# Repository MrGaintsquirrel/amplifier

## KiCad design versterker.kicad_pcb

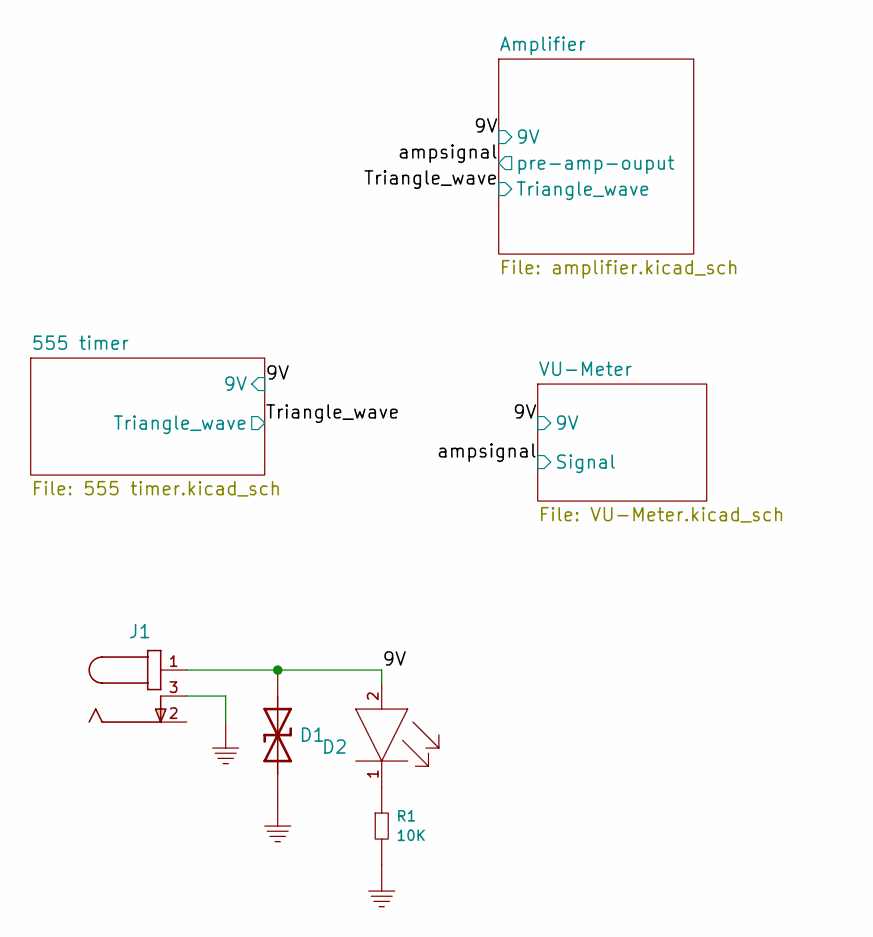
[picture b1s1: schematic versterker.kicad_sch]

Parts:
D1: D_SMCJ9.0CA_TVS; D_9V_TVS_SMCJ-Q; PARTREV 11/20/15; Mouser 576-SMCJ9.0CA
D2: D_RED_0603_Wurth_150060RS75000; D_RED_0603_Wurth; Mouser 710-150060RS75000
J1: J_Barreljack_3.5mm_Wurth_TH; J_Barreljack_3.5mm_Wurth; Mouser 710-694102303002
R1: R_10K_0603; R_0603; Mouser 667-ERJ-UP3F1002V

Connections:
/9V: D1.1, D2.2 (ANODE), J1.1; also elsewhere on the board
GND: D1.2, J1.3, R1.2; also elsewhere on the board
unnamed: D2.1 (CATHODE), R1.1

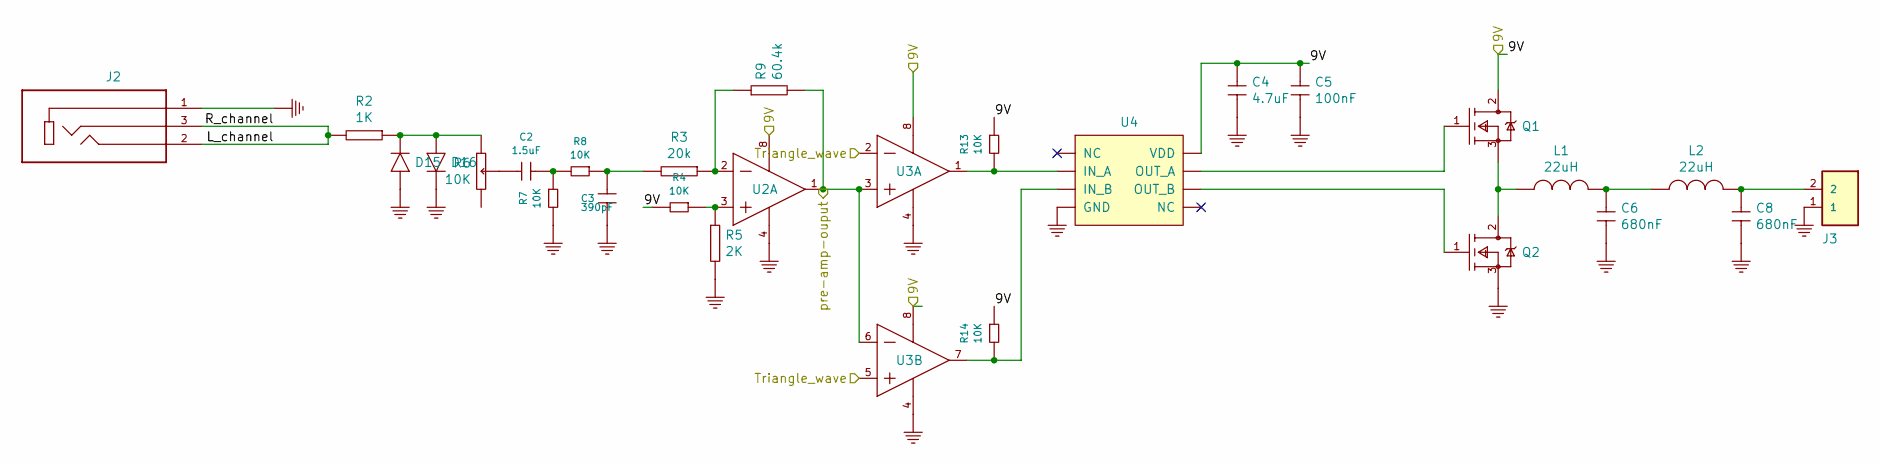
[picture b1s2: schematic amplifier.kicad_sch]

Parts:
C2: C_1.5uF_0603_25V; C_0603; Mouser 810-C1608X5R1E155K
C3: C_390pF_0603_50V; C_0603; Mouser 80-C0603C391K5R
C4: C_4.7uF_0603_25V; C_0603; Mouser 963-TMK107BBJ475KA-T
C5: C_100nF_0603_25V; C_0603; Mouser 810-C0603X5R1E104KBB
C6, C8: C_680nF_TH_450V; C_ECWFD_Panasonic; Mouser 667-ECW-FD2W684J
D15, D16: D_1N4148WS_SOD323F_ONSEMI; D_1N4148_SOD-323F_ONSEMI; Mouser 512-1N4148WS
J2: J_3.5mm_jack_SJ1-3523N; CUI_SJ1-3523N; Mouser 490-SJ1-3523N
J3: J_2_screwterminal_2.54_282834-2; J_2_screwterminal_2.54; Mouser 571-282834-2
L1, L2: L_22uH_RFS1113_coilcraft_TH; L_RFS1113_coilcraft; Mouser 994-RFS1113-223ME
Q1, Q2: Q_IRFZ44NPBF_N-Channel_Infineon; Q_IRFZ44NPBF_Infineon; Mouser 942-IRFZ44NPBF
R2: R_1K_0603; R_0603; Mouser 667-ERJ-PB3D1001V
R3: R_20K_0603; R_0603; Mouser 603-RT0603FRE0720KL
R4, R7, R8, R13, R14: R_10K_0603; R_0603; Mouser 667-ERJ-UP3F1002V
R5: R_2K_0603; R_0603; Mouser 603-RT0603BRD072KL
R6: R_10K_Potmeter; R_TH_POT_P160series
R9: R_60.4K_0603; R_0603; Mouser 603-RT0603DRE0760K4L
U2: U_LM358AP_TI_DIP; Mouser 926-LM358N/NOPB
U3: U_LM393N_NOPB; U_TI_LM393N_NOPB; Mouser 926-LM393N/NOPB
U4: U_TC4427M_Microchip; U_8_DIP_TC4427CPA_Microchip; Mouser 579-TC4427ACPA

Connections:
/9V: C4.1, C5.1, Q1.2 (DRAIN), R4.2, R13.1, R14.1, U2.8 (VCC), U3.8 (V+), U4.6 (VDD); also elsewhere on the board
/Amplifier/L_channel: J2.2, J2.3, R2.2
/Triangle_wave: U3.2 (INA-), U3.5 (INB+); also elsewhere on the board
/ampsignal: R9.2, U2.1 (1OUT), U3.3 (INA+), U3.6 (INB-); also elsewhere on the board
GND: C3.2, C4.2, C5.2, C6.2, C8.2, D15.A, D16.C, J2.1, J3.1, Q2.3 (SOURCE), R5.2, R7.2, U2.4 (GND), U3.4 (GND), U4.3 (GND); also elsewhere on the board
unnamed: C2.1, R7.1, R8.2
unnamed: C2.2, R6.2 (S)
unnamed: C3.1, R3.2, R8.1
unnamed: C6.1, L1.2, L2.1
unnamed: C8.1, J3.2, L2.2
unnamed: D15.C, D16.A, R2.1, R6.1
unnamed: L1.1, Q1.3 (SOURCE), Q2.2 (DRAIN)
unnamed: Q1.1 (GATE), U4.7 (OUT_A)
unnamed: Q2.1 (GATE), U4.5 (OUT_B)
unnamed: R3.1, R9.1, U2.2 (1IN-)
unnamed: R4.1, R5.1, U2.3 (1IN+)
unnamed: R13.2, U3.1 (OUTA), U4.2 (IN_A)
unnamed: R14.2, U3.7 (OUTB), U4.4 (IN_B)

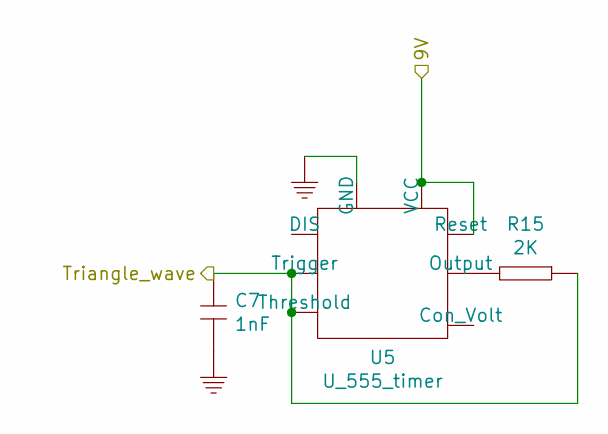
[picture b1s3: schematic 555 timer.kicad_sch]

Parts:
C7: C_1nF_0603_50V; C_0603; Mouser 603-CC603MRX7R9BB102
R15: R_2K_0603; R_0603; Mouser 603-RT0603BRD072KL
U5: U_555_timer; U_LM555CN

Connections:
/9V: U5.4 (Reset), U5.8 (VCC); also elsewhere on the board
/Triangle_wave: C7.1, R15.1, U5.2 (Trigger), U5.6 (Threshold); also elsewhere on the board
GND: C7.2, U5.1 (GND); also elsewhere on the board
unnamed: R15.2, U5.3 (Output)

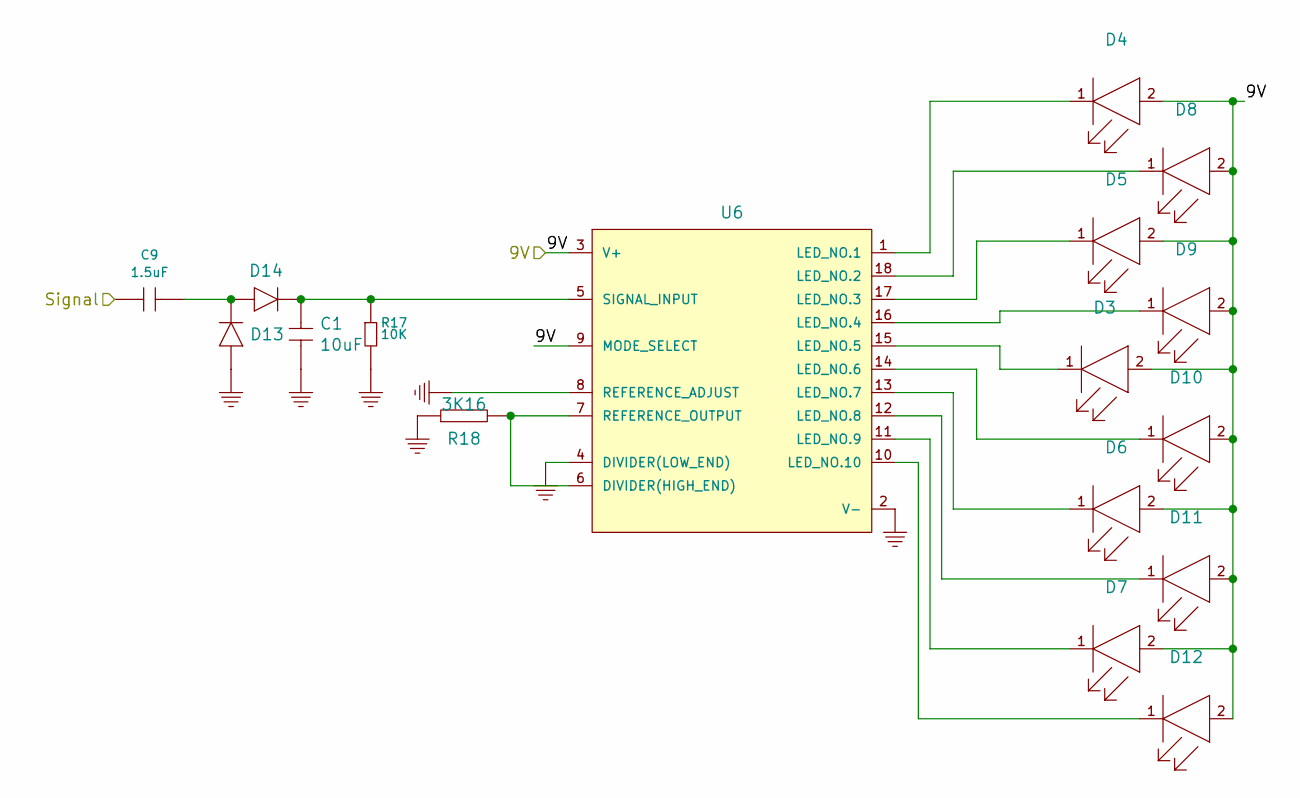
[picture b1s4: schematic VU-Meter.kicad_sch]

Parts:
C1: C_10uF_0603_16V; C_0603; Mouser 187-CL10A106KO8NQNC
C9: C_1.5uF_0603_25V; C_0603; Mouser 810-C1608X5R1E155K
D3, D4, D5, D6, D7, D8, D9, D10, D11, D12: D_RED_0603_Wurth_150060RS75000; D_RED_0603_Wurth; Mouser 710-150060RS75000
D13, D14: D_1N4148WS_SOD323F_ONSEMI; D_1N4148_SOD-323F_ONSEMI; Mouser 512-1N4148WS
R17: R_10K_0603; R_0603; Digi-key YAG1236CT-ND
R18: R_3K16_0603; R_0603; Mouser 603-RT0603BRD073K16L
U6: U_LM3914N-1_NOPB; U_LM3914_TI_DIP; Mouser 926-LM3914N-1/NOPB

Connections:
/9V: D3.2 (ANODE), D4.2 (ANODE), D5.2 (ANODE), D6.2 (ANODE), D7.2 (ANODE), D8.2 (ANODE), D9.2 (ANODE), D10.2 (ANODE), D11.2 (ANODE), D12.2 (ANODE), U6.3 (V+), U6.9 (MODE_SELECT); also elsewhere on the board
/ampsignal: C9.2; also elsewhere on the board
GND: C1.2, D13.A, R17.2, R18.1, U6.2 (V-), U6.4 (DIVIDER(LOW_END)), U6.8 (REFERENCE_ADJUST); also elsewhere on the board
unnamed: C1.1, D14.C, R17.1, U6.5 (SIGNAL_INPUT)
unnamed: C9.1, D13.C, D14.A
unnamed: D3.1 (CATHODE), U6.15 (LED_NO.5)
unnamed: D4.1 (CATHODE), U6.1 (LED_NO.1)
unnamed: D5.1 (CATHODE), U6.17 (LED_NO.3)
unnamed: D6.1 (CATHODE), U6.13 (LED_NO.7)
unnamed: D7.1 (CATHODE), U6.11 (LED_NO.9)
unnamed: D8.1 (CATHODE), U6.18 (LED_NO.2)
unnamed: D9.1 (CATHODE), U6.16 (LED_NO.4)
unnamed: D10.1 (CATHODE), U6.14 (LED_NO.6)
unnamed: D11.1 (CATHODE), U6.12 (LED_NO.8)
unnamed: D12.1 (CATHODE), U6.10 (LED_NO.10)
unnamed: R18.2, U6.6 (DIVIDER(HIGH_END)), U6.7 (REFERENCE_OUTPUT)

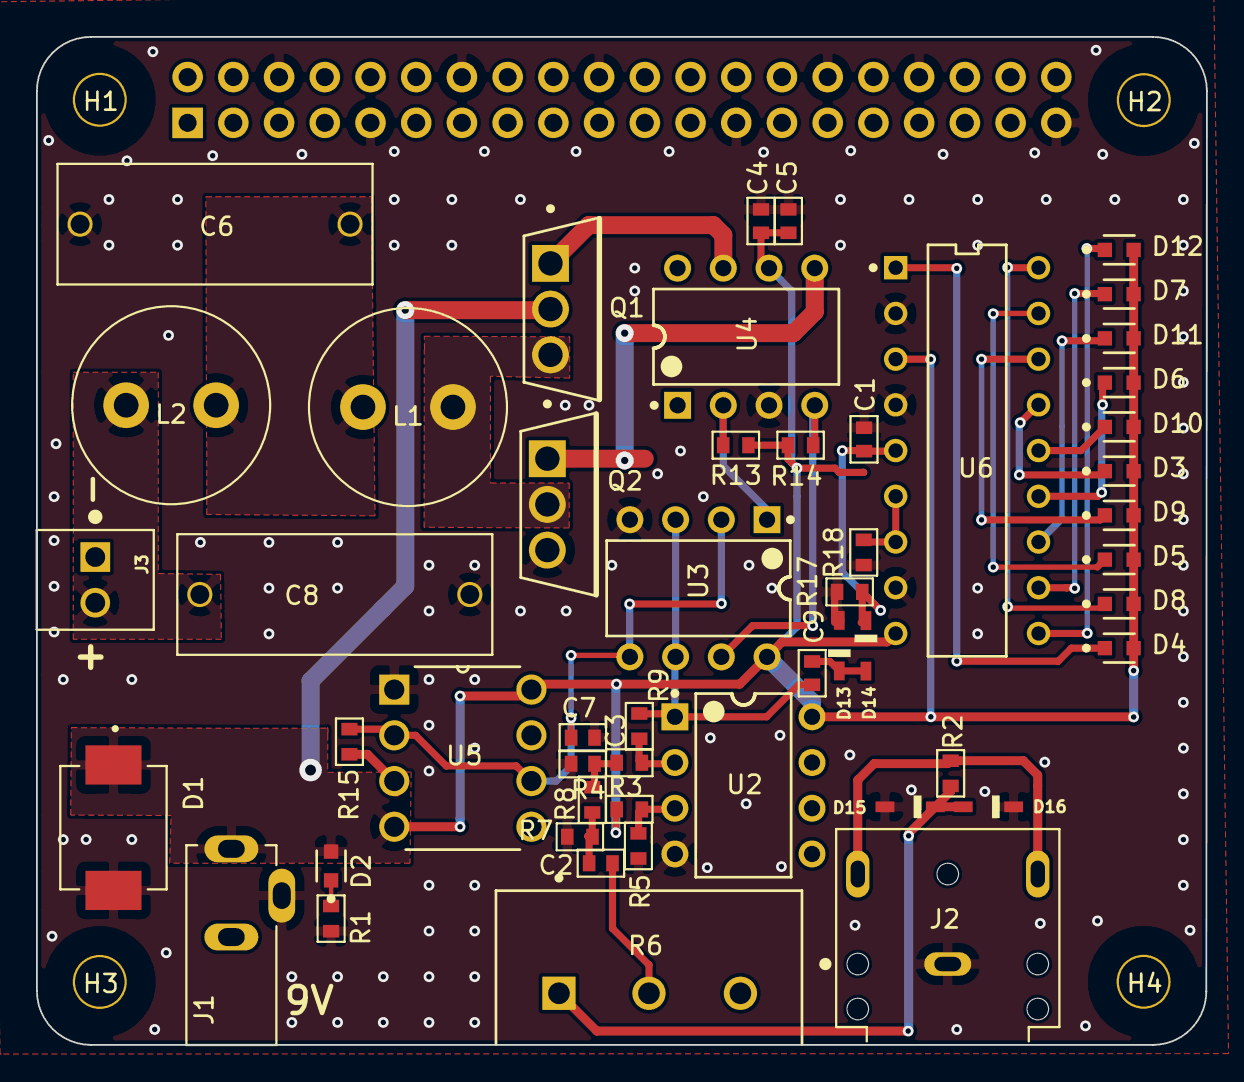
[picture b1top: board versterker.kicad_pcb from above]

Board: 2 copper layers, 65.0 x 56.0 mm, 56 parts (1 on the bottom side), 34 nets.

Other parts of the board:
H1, H2, H3, H4: 3mm_Mounting_Hole; NPTH_3mm_ID
J3#2: 40HAT; PinSocket_2x20_P2.54mm_Vertical

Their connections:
/P5V_HAT: J3#2.2, J3#2.4
GND: J3#2.6, J3#2.9, J3#2.14, J3#2.20, J3#2.25, J3#2.30, J3#2.34, J3#2.39; also elsewhere on the board

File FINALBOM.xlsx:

Ref | Qnty | Waarde | Cmp name | Footprint | Description | Mouser
C1, | 1 | C_10uF_0603_16V | C_10uF_0603_16V | MAIN_PCB_LIB:C_0603 |  | 187-CL10A106KO8NQNC
C2,C9, | 2 | C_1.5uF_0603_25V | C_1.5uF_0603_25V | MAIN_PCB_LIB:C_0603 |  | 810-C1608X5R1E155K
C3, | 1 | C_390pF_0603_50V | C_390pF_0603_50V | MAIN_PCB_LIB:C_0603 |  | 80-C0603C391K5R
C4, | 1 | C_4.7uF_0603_25V | C_4.7uF_0603_25V | Main_LIB:C_0603 |  | 963-TMK107BBJ475KA-T
C5, | 1 | C_100nF_0603_25V | C_100nF_0603_25V | MAIN_PCB_LIB:C_0603 |  | 810-C0603X5R1E104KBB
C6,C8, | 2 | C_680nF_TH_450V | C_680nF_TH_450V | MAIN_PCB_LIB:C_ECWFD_Panasonic |  | 667-ECW-FD2W684J
C7, | 1 | C_1nF_0603_50V | C_1nF_0603_50V | MAIN_PCB_LIB:C_0603 |  | 581-06035A102J
D1, | 1 | D_SMCJ9.0CA_TVS | D_SMCJ9.0CA_TVS | MAIN_PCB_LIB:D_9V_TVS_SMCJ-Q |  | 576-SMCJ9.0CA
D2,D3,D4,D5,D6,D7,D8,D9,D10,D11,D12, | 11 | D_RED_0603_Wurth_150060RS75000 | D_RED_0603_Wurth_150060RS75000 | MAIN_PCB_LIB:D_RED_0603_Wurth |  | 710-150060RS75000
D13,D14,D15,D16, | 4 | D_1N4148WS_SOD323F_ONSEMI | D_1N4148WS_SOD323F_ONSEMI | MAIN_PCB_LIB:D_1N4148_SOD-323F_ONSEMI |  | 512-1N4148WS
J1, | 1 | J_Barreljack_3.5mm_Wurth_TH | J_Barreljack_3.5mm_Wurth_TH | MAIN_PCB_LIB:J_Barreljack_3.5mm_Wurth |  | 710-694102303002
J2, | 1 | J_3.5mm_jack_SJ1-3523N | J_3.5mm_jack_SJ1-3523N | CUI_SJ1-3523N |  | 490-SJ1-3523N
J3, | 1 | J_2_screwterminal_2.54_282834-2 | J_2_screwterminal_2.54_282834-2 | MAIN_PCB_LIB:J_2_screwterminal_2.54 |  | 571-282834-2
L1,L2, | 2 | L_22uH_RFS1113_coilcraft_TH | L_22uH_RFS1113_coilcraft_TH | MAIN_PCB_LIB:L_RFS1113_coilcraft |  | 994-RFS1113-223ME
Q1,Q2, | 2 | Q_IRFZ44NPBF_N-Channel_Infineon | Q_IRFZ44NPBF_N-Channel_Infineon | MAIN_PCB_LIB:Q_IRFZ44NPBF_Infineon |  | 942-IRFZ44NPBF
R1,R4,R7,R8,R13,R14,R17, | 7 | R_10K_0603 | R_10K_0603 | MAIN_PCB_LIB:R_0603 |  | 603-AC0603FR-1010KL
R2, | 1 | R_1K_0603 | R_1K_0603 | MAIN_PCB_LIB:R_0603 |  | 603-AC0603FR-071KL
R3, | 1 | R_20K_0603 | R_20K_0603 | MAIN_PCB_LIB:R_0603 |  | 603-RT0603FRE0720KL
R5,R15, | 2 | R_2K_0603 | R_2K_0603 | MAIN_PCB_LIB:R_0603 |  | 603-RT0603FRE072KL
R6, | 1 | R_10K_Potmeter | R_10K_Potmeter | MAIN_PCB_LIB:R_TH_POT_P160series
R9, | 1 | R_60.4K_0603 | R_60.4K_0603 | MAIN_PCB_LIB:R_0603 |  | 603-RT0603DRE0760K4L
R18, | 1 | R_3K16_0603 | R_3K16_0603 | MAIN_PCB_LIB:R_0603 |  | 603-RT0603BRD073K16L
U2, | 1 | U_LM358AP_TI_DIP | U_LM358AP_TI_DIP | MAIN_PCB_LIB:U_LM358AP_TI_DIP |  | 926-LM358N/NOPB
U3, | 1 | U_LM393N_NOPB | U_LM393N_NOPB | MAIN_PCB_LIB:U_TI_LM393N_NOPB |  | 926-LM393N/NOPB
U4, | 1 | U_TC4427M_Microchip | U_TC4427M_Microchip | MAIN_PCB_LIB:U_8_DIP_TC4427CPA_Microchip |  | 579-TC4427ACPA
U5, | 1 | U_555_timer | U_555_timer | MAIN_PCB_LIB:U_LM555CN
U6, | 1 | U_LM3914N-1_NOPB | U_LM3914N-1_NOPB | MAIN_PCB_LIB:U_LM3914_TI_DIP |  | 926-LM3914N-1/NOPB

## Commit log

2021-10-14 added mosfet and driver
2021-10-18 added bandpass filter
2021-10-18 added filter end stage
2021-10-19 created pcb
2021-11-21 changes made
2021-11-21 changed vu meter resistor value's
2021-12-05 no message
2021-12-06 added raspberry pi hat pcb outline and layout
2021-12-06 changed everything to 9V and changed inductor to match one in stock
2021-12-09 changed vu meter circuit
2021-12-10 routed pcb
2021-12-10 made schematic changed based on testing
2021-12-11 made gerbers
2021-12-17 changed gerbers after receiving pcb
2021-12-18 changed partnumbers
2022-01-10 changed to new kicad6
